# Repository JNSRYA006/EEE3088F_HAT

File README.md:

# Autonomous Plant Monitoring HAT for Discovery Board with STM32F051x8
This repository will be updated at each stage of the design process, and where necessary changes are made.

# Group Members:
* Ryan Jones (JNSRYA006)
* Alex Cargill (CRGALE002)
* Devlin Trafford (TRFDEV001)

# Project Details
### This project is part of a project for EEE3088F in 2022
This project will design a HAT *(Hardware Attached on Top)* for a STM Discovery Board which uses the STM32F051x8. The use case for this HAT is for semi-autonomous indoor plant growing. It will have a temperature sensor located as close to the plant as possible as well as a light sensor facing the main direction which the plant receives light from . These sensors will connect to a STM Discovery board, which will act as the brain of the system. This design was created for small scale agricultural setups. Appropriate user stories were applied to develop the Specifications. Given these use cases, the PCB is able to:

* Monitor the **temperature** around a plant
* Get precise readings of the **light level** a plant is receiving. 

See a 3D render of the PCB from KiCad below,

|  |
| :----------------------------------------------------------: |

## Repository Structure
### Each sub-folder contains different aspects relating to different parts of the project
* ***PCB:*** The KiCad Project, Schematics, PCB & Layout and Project Libraries
* ***Firmware:*** Any software developed for the hardware or instructions on where to find relevant sofware in cases where it makes more sense to have this in its own dedicated repo
* ***Docs:***  Project documentation, Draft documents, ERC & DRC reports, project handins, schematic screenshot & documents and component datasheets
* ***Production:*** The final gerber files, BOM, Budget, or anything required by the fabrication houses
* ***Simulation:*** Any simulation files (SPICE) or design stage generated results (matlab or excel) 
* ***CAD:*** Any 3D models or mechanical designs for enclosures or support
# Hardware Requirements
 * [ ] STMDiscovery Board with an STM32F051x8 μC
 * [ ] 1 x MicroUSB to USB-A Cable
 * [ ] 1x MiniUSB to USB-A Cable
 * [ ] 8x Male to Female Jumpers

# Software Requirements

 - [ ] Computer 
	 - *Windows, Linux or MACOS*
 - [ ] STM32Cube IDE
	 - [Download available online](https://www.st.com/en/development-tools/stm32cubeide.html#get-software)
 - [ ] PuTTY
	 - [Download available online](https://www.chiark.greenend.org.uk/~sgtatham/putty/latest.html)

# How to short the UVLO circuit

- On the LHS of the board, remove resistor **R12 & R10** using pliers and twisting and pulling the resistors

- Q1 & IC1 (Circled in **Orange**) are the MOSFET & Op-Amp in the UVLO circuit that needs to be removed by soldering one end of a wire to the top pad (Pad 2) of R12 to the top pad (Pad 2) of R10 (Circled in **Green**)

  |  |
  | :----------------------------------------------------------: |

# How to connect the power module to the rest of the board

- On the top, RHS of the board, solder a wire between **TP9** *OR* the **+3V** pin pad and the right hand pin of **J7**
  - This will connect the power from the power module to the rest of the circuit
- If connected correctly, when a battery is inserted or a USB is connected, a **Red** diode (**D9**) will turn on to indicate the sensing and microcontroller sub-circuits are receiving power.

# How to connect the PCB to the STMDiscovery Board

The following locations **on the PCB** need to be soldered to the male end of the jumper:

(*Refer to the KiCad PCB file [here](https://github.com/JNSRYA006/EEE3088F_HAT/blob/main/PCB/main/main.kicad_pcb) for the exact location of these*)

- PA1
- PA2
- PA9
- PA10
- PB6
- PB7

The female end of these jumpers are then connected to the corresponding pins on the STMDiscovery board.

# How to connect the PCB & STMDiscovery to your computer using UART

- Download and install CH340 drivers
  - [Download available online](https://learn.sparkfun.com/tutorials/how-to-install-ch340-drivers/all#drivers-if-you-need-them)
- Plug the device to your computer using a USB port. 
  - Check that the device is visible under ports in the Device Manager (for *Windows*), 
    - [Instructions on how to open Device Manager here](https://www.lifewire.com/how-to-open-device-manager-2626075)
- Create a serial connection with a baud rate of 18400bits/s in PuTTY

# How to send your first data to the board!

- After connecting the board using the above instructions,
- Type “Hello HAT” into the console and press ENTER.
- The device will dump all information collected since the last time the device was connected to a USB host device in the terminal window

# Contributing to this project

You're more than welcome to contribute to this project! Please take a look at our CONTRIBUTING.md file linked here

# License

[Creative Commons Attribution 4.0 International license](https://choosealicense.com/licenses/cc-by-4.0/)

[MIT License](https://choosealicense.com/licenses/mit/)

#

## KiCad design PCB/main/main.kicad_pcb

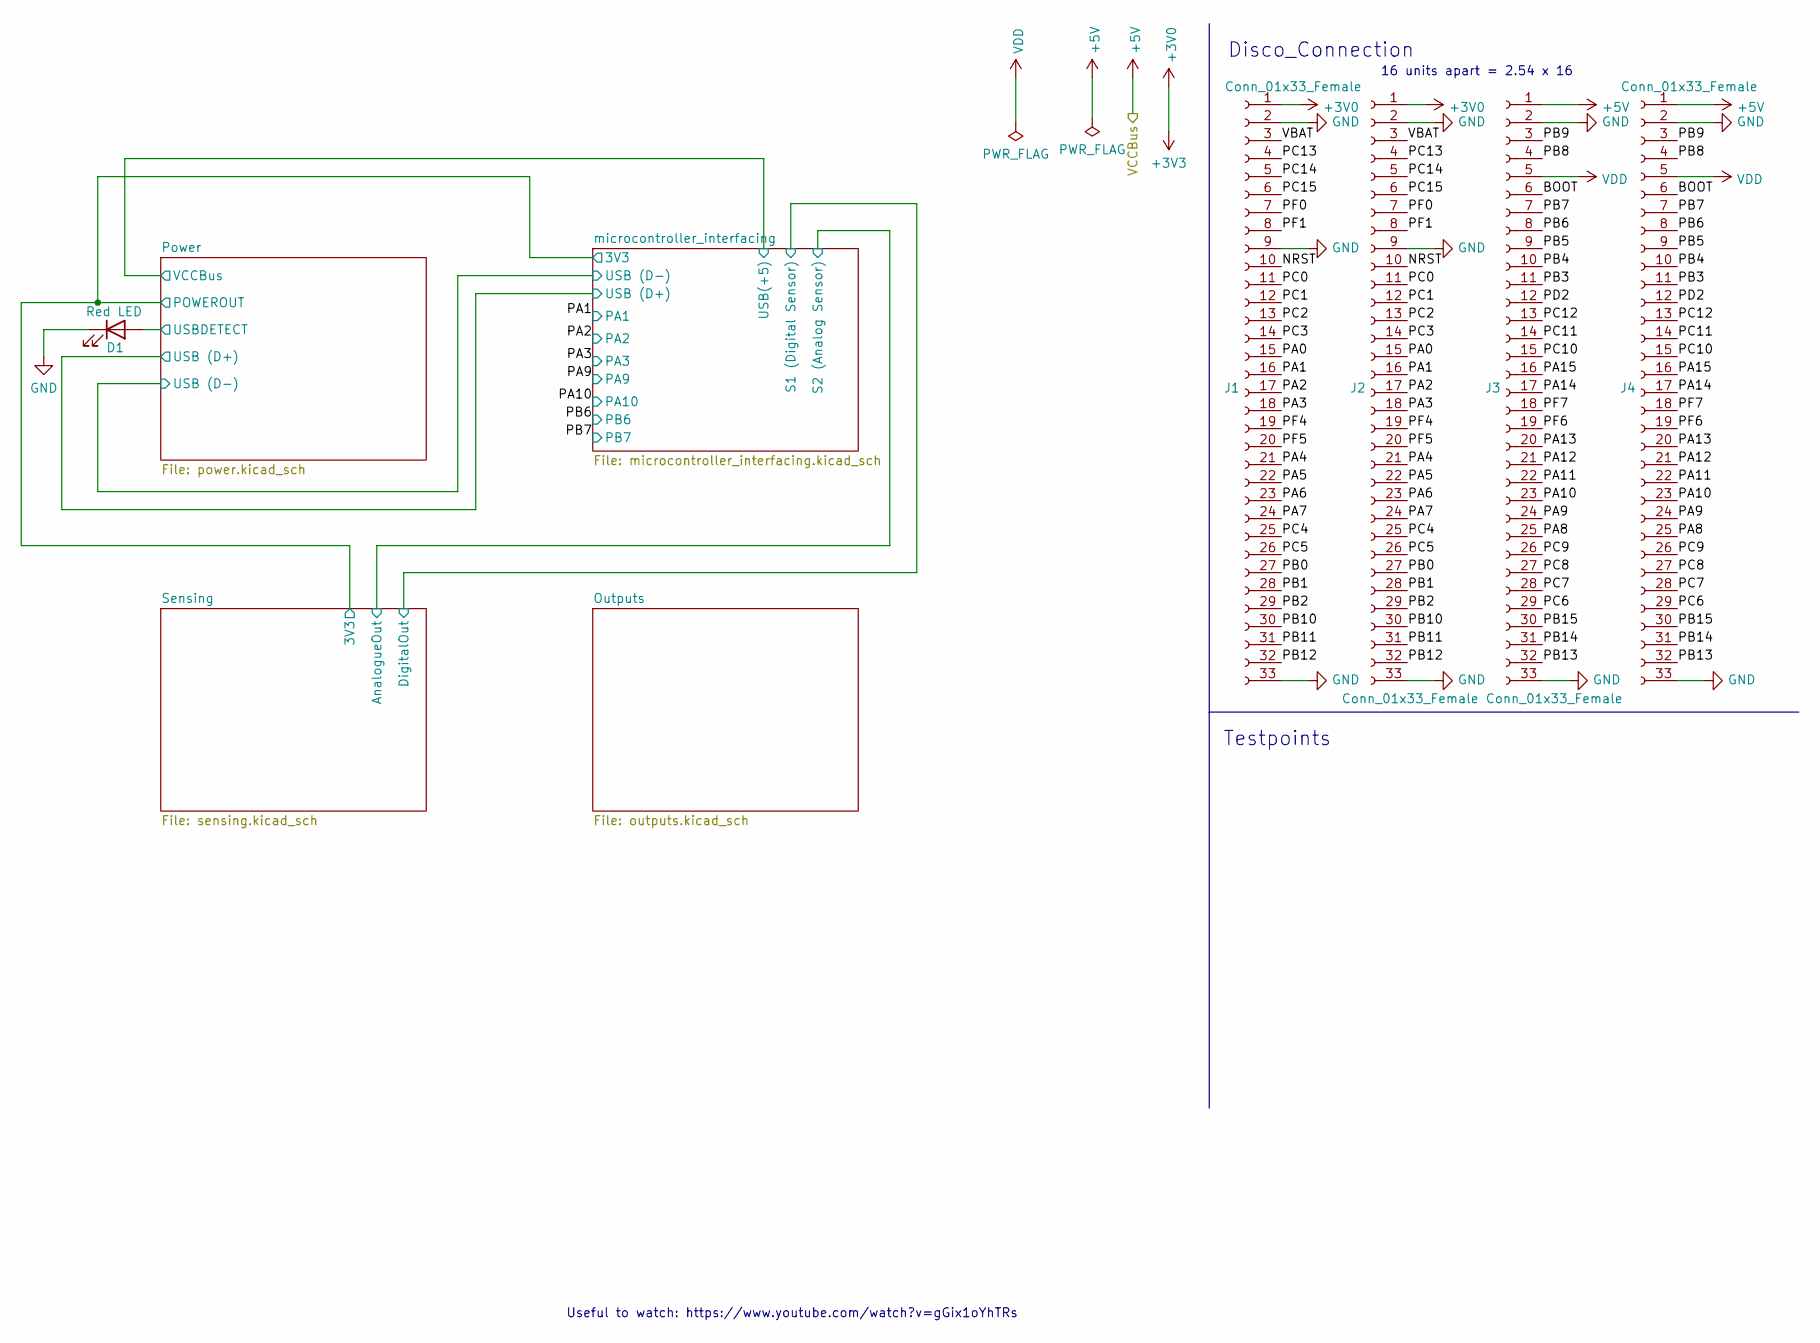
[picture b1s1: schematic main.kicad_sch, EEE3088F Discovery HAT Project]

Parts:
D1: Red LED; LEDC1608X70N; JLC Part Number C84256
J1, J4: Conn_01x33_Female; PinHeader_1x33_P2.54mm_Vertical
J2, J3: Conn_01x33_Female; PinSocket_1x33_P2.54mm_Vertical; LCSC C1234 (example)

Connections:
+3V0: J1.1, J2.1; also elsewhere on the board
+5V: J3.1, J4.1; also elsewhere on the board
/BOOT: J3.6, J4.6
/NRST: J1.10, J2.10
/PA0: J1.15, J2.15
/PA1: J1.16, J2.16; also elsewhere on the board
/PA2: J1.17, J2.17; also elsewhere on the board
/PA3: J1.18, J2.18; also elsewhere on the board
/PA4: J1.21, J2.21
/PA5: J1.22, J2.22
/PA6: J1.23, J2.23
/PA7: J1.24, J2.24
/PA8: J3.25, J4.25
/PA9: J3.24, J4.24; also elsewhere on the board
/PA10: J3.23, J4.23; also elsewhere on the board
/PA11: J3.22, J4.22
/PA12: J3.21, J4.21
/PA13: J3.20, J4.20
/PA14: J3.17, J4.17
/PA15: J3.16, J4.16
/PB0: J1.27, J2.27
/PB1: J1.28, J2.28
/PB2: J1.29, J2.29
/PB3: J3.11, J4.11
/PB4: J3.10, J4.10
/PB5: J3.9, J4.9
/PB6: J3.8, J4.8; also elsewhere on the board
/PB7: J3.7, J4.7; also elsewhere on the board
/PB8: J3.4, J4.4
/PB9: J3.3, J4.3
/PB10: J1.30, J2.30
/PB11: J1.31, J2.31
/PB12: J1.32, J2.32
/PB13: J3.32, J4.32
/PB14: J3.31, J4.31
/PB15: J3.30, J4.30
/PC0: J1.11, J2.11
/PC1: J1.12, J2.12
/PC2: J1.13, J2.13
/PC3: J1.14, J2.14
/PC4: J1.25, J2.25
/PC5: J1.26, J2.26
/PC6: J3.29, J4.29
/PC7: J3.28, J4.28
/PC8: J3.27, J4.27
/PC9: J3.26, J4.26
/PC10: J3.15, J4.15
/PC11: J3.14, J4.14
/PC12: J3.13, J4.13
/PC13: J1.4, J2.4
/PC14: J1.5, J2.5
/PC15: J1.6, J2.6
/PD2: J3.12, J4.12
/PF0: J1.7, J2.7
/PF1: J1.8, J2.8
/PF4: J1.19, J2.19
/PF5: J1.20, J2.20
/PF6: J3.19, J4.19
/PF7: J3.18, J4.18
/Power/USBDETECT: D1.2 (A); also elsewhere on the board
/VBAT: J1.3, J2.3
GND: D1.1 (K), J1.2, J1.9, J1.33, J2.2, J2.9, J2.33, J3.2, J3.33, J4.2, J4.33; also elsewhere on the board
VDD: J3.5, J4.5

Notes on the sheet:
Useful to watch: https://www.youtube.com/watch?v=gGix1oYhTRs
16 units apart = 2.54 x 16
Disco_Connection
Testpoints

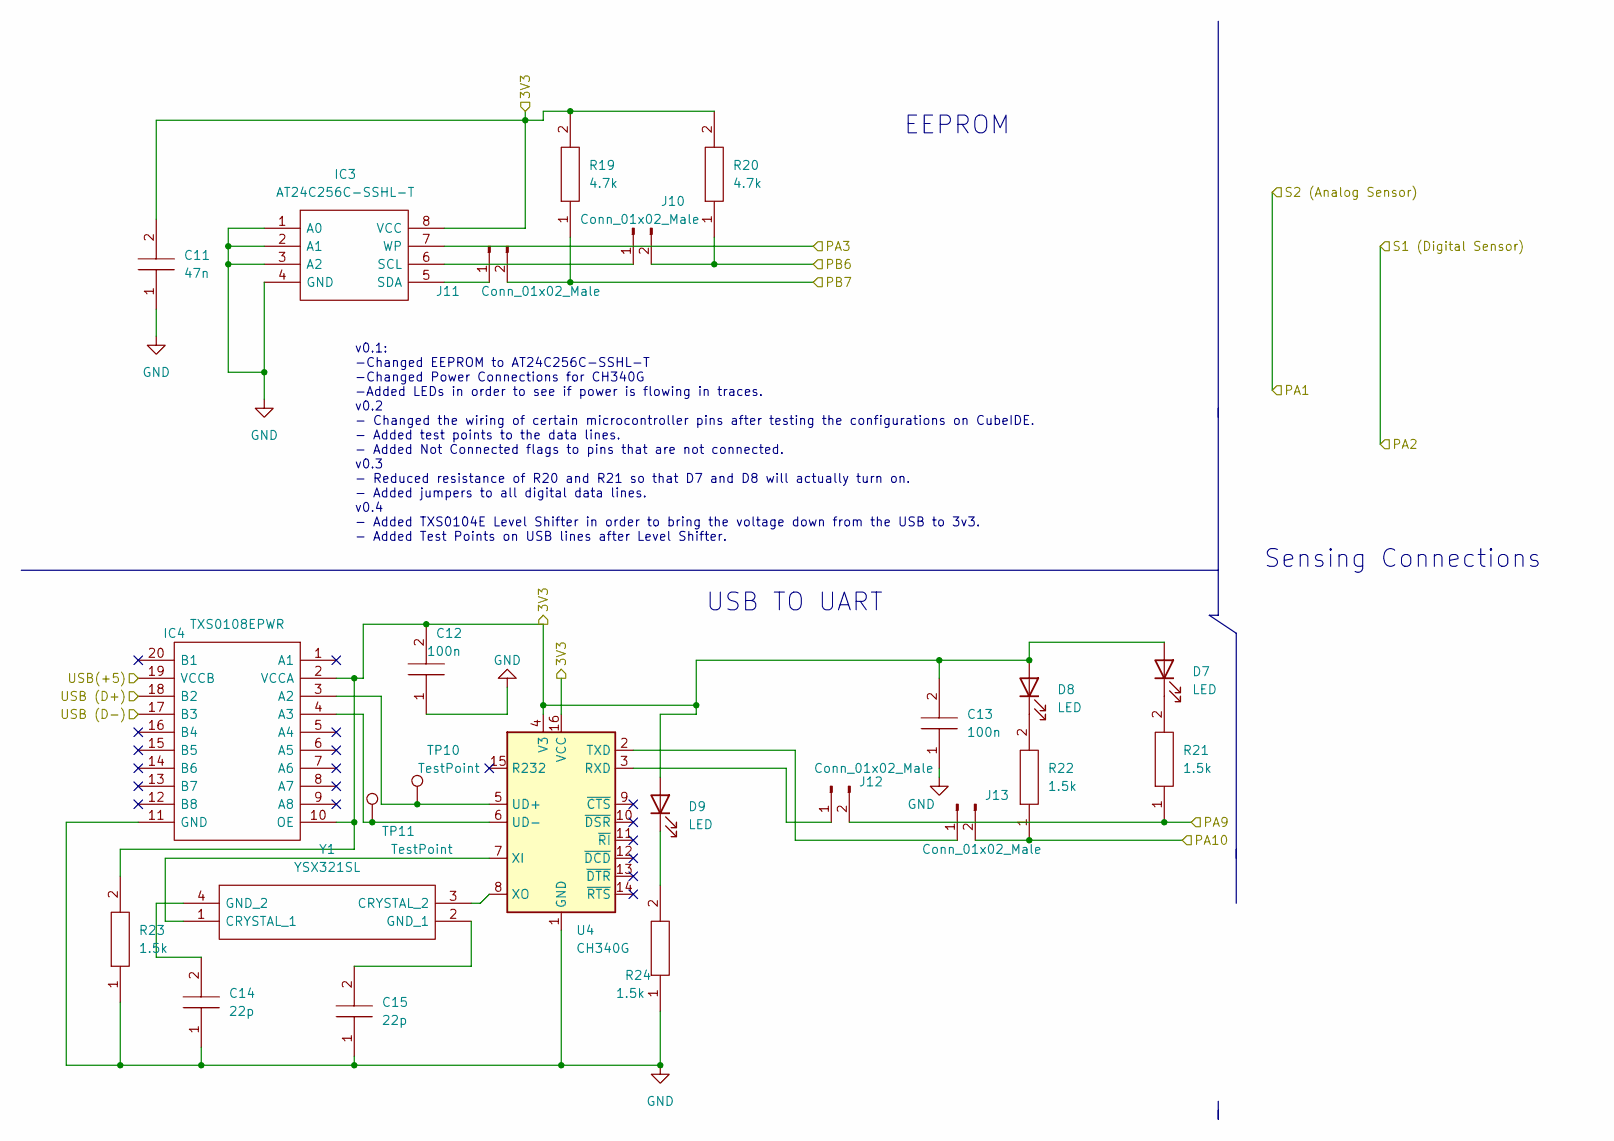
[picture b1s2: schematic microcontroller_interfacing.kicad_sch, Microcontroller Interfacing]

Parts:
C11: 47n; CAPC1608X90N; Manufacturer_Part_Number CL05B104KO5NNNC; Mouser Part Number 187-CL05B104KO5NNNC
C12, C13: 100n; C_0402_1005Metric; Manufacturer_Part_Number CL05B104KO5NNNC; Mouser Part Number 187-CL05B104KO5NNNC
C14, C15: 22p; CAPC1608X90N; Manufacturer_Part_Number CL05B104KO5NNNC; Mouser Part Number 187-CL05B104KO5NNNC
D7, D8, D9: LED; LED_0805_2012Metric; JLC Part Number C2286
IC3: AT24C256C-SSHL-T; SOIC127P600X175-8N; JLC Part Number C6482
IC4: TXS0108EPWR; SOP65P640X120-20N; Manufacturer_Part_Number TXS0108EPWR; Mouser Part Number 595-TXS0108EPWR
J10, J11, J12, J13: Conn_01x02_Male; 53398-0271; JLC Part Number C122410
R19, R20: 4.7k; RESC2013X65N; Manufacturer_Part_Number 0402WGF4701TCE
R21, R22, R23, R24: 1.5k; RESC2013X65N; Manufacturer_Part_Number 0402WGF4701TCE; JLC Part Number C25867
TP10, TP11: TestPoint; TestPoint_Pad_D2.0mm
U4: CH340G; SOIC127P600X180-16N; JLC Part Number C14267
Y1: YSX321SL; Manufacturer_Part_Number YSX321SL; JLC Part Number C9002

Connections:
+3V3: C11.2, C12.2, C13.2, D7.2 (A), D8.2 (A), D9.2 (A), IC3.8 (VCC), IC4.2 (VCCA), IC4.10 (OE), R19.2, R20.2, R23.2, U4.4 (V3), U4.16 (VCC); also elsewhere on the board
+5V: IC4.19 (VCCB); also elsewhere on the board
/PA3: IC3.7 (WP); also elsewhere on the board
/PA9: J12.2, R21.1; also elsewhere on the board
/PA10: J13.2, R22.1; also elsewhere on the board
/PB6: J10.2, R20.1; also elsewhere on the board
/PB7: J11.2, R19.1; also elsewhere on the board
/Power/USB (D+): IC4.18 (B2); also elsewhere on the board
/Power/USB (D-): IC4.17 (B3); also elsewhere on the board
GND: C11.1, C12.1, C13.1, C14.1, C15.1, IC3.1 (A0), IC3.2 (A1), IC3.3 (A2), IC3.4 (GND), IC4.11 (GND), R23.1, R24.1, U4.1 (GND); also elsewhere on the board
unnamed: C14.2, Y1.4 (GND_2)
unnamed: C15.2, Y1.2 (GND_1)
unnamed: D7.1 (K), R21.2
unnamed: D8.1 (K), R22.2
unnamed: D9.1 (K), R24.2
unnamed: IC3.5 (SDA), J11.1
unnamed: IC3.6 (SCL), J10.1
unnamed: IC4.3 (A2), TP10.1, U4.5 (UD+)
unnamed: IC4.4 (A3), TP11.1, U4.6 (UD-)
unnamed: J12.1, U4.3 (RXD)
unnamed: J13.1, U4.2 (TXD)
unnamed: U4.7 (XI), Y1.1 (CRYSTAL_1)
unnamed: U4.8 (XO), Y1.3 (CRYSTAL_2)

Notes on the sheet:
v0.1: -Changed EEPROM to AT24C256C-SSHL-T -Changed Power Connections for CH340G -Added LEDs in order to see if power is flowing in traces. v0.2 - Changed the wiring of certain microcontroller pins after testing the configurations on CubeIDE. - Added test points to the data lines. - Added Not Connec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
EEPROM
USB TO UART
Sensing Connections

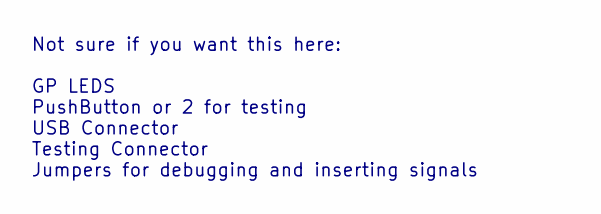
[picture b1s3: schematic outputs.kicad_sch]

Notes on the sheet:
Not sure if you want this here: GP LEDS PushButton or 2 for testing USB Connector Testing Connector Jumpers for debugging and inserting signals

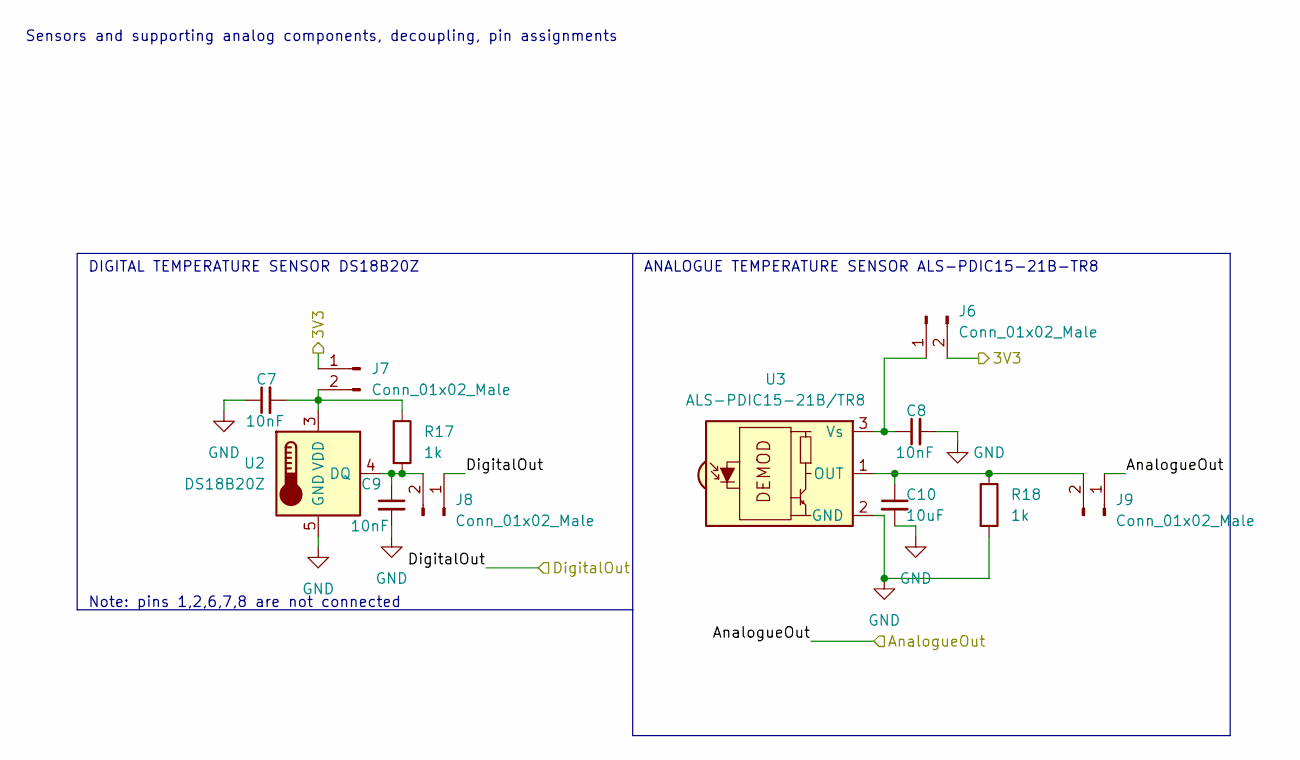
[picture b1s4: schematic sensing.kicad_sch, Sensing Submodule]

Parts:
C7, C8, C9: 10nF; C_0402_1005Metric; JLC Part Number C15195
C10: 10uF; CAPC2012X145N; JLC Part Number C19702
J6, J7, J8, J9: Conn_01x02_Male; 53398-0271; JLC Part Number C122410
R17, R18: 1k; RESC1608X55N; JLC Part Number C21190
U2: DS18B20Z; SOIC-8_3.9x4.9mm_P1.27mm; JLC Part Number C695837
U3: ALS-PDIC15-21B/TR8; LED-SMD_1206-4P-L3.2-W1.5-TR; JLC Part Number C131243

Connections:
+3V3: J6.2, J7.1; also elsewhere on the board
/PA1: J9.1; also elsewhere on the board
/PA2: J8.1; also elsewhere on the board
GND: C7.1, C8.2, C9.2, C10.2, R18.2, U2.5 (GND), U3.2 (GND); also elsewhere on the board
unnamed: C7.2, J7.2, R17.1, U2.3 (VDD)
unnamed: C8.1, J6.1, U3.3 (Vs)
unnamed: C9.1, J8.2, R17.2, U2.4 (DQ)
unnamed: C10.1, J9.2, R18.1, U3.1 (OUT)

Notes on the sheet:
ANALOGUE TEMPERATURE SENSOR ALS-PDIC15-21B-TR8
DIGITAL TEMPERATURE SENSOR DS18B20Z
Note: pins 1,2,6,7,8 are not connected
Sensors and supporting analog components, decoupling, pin assignments

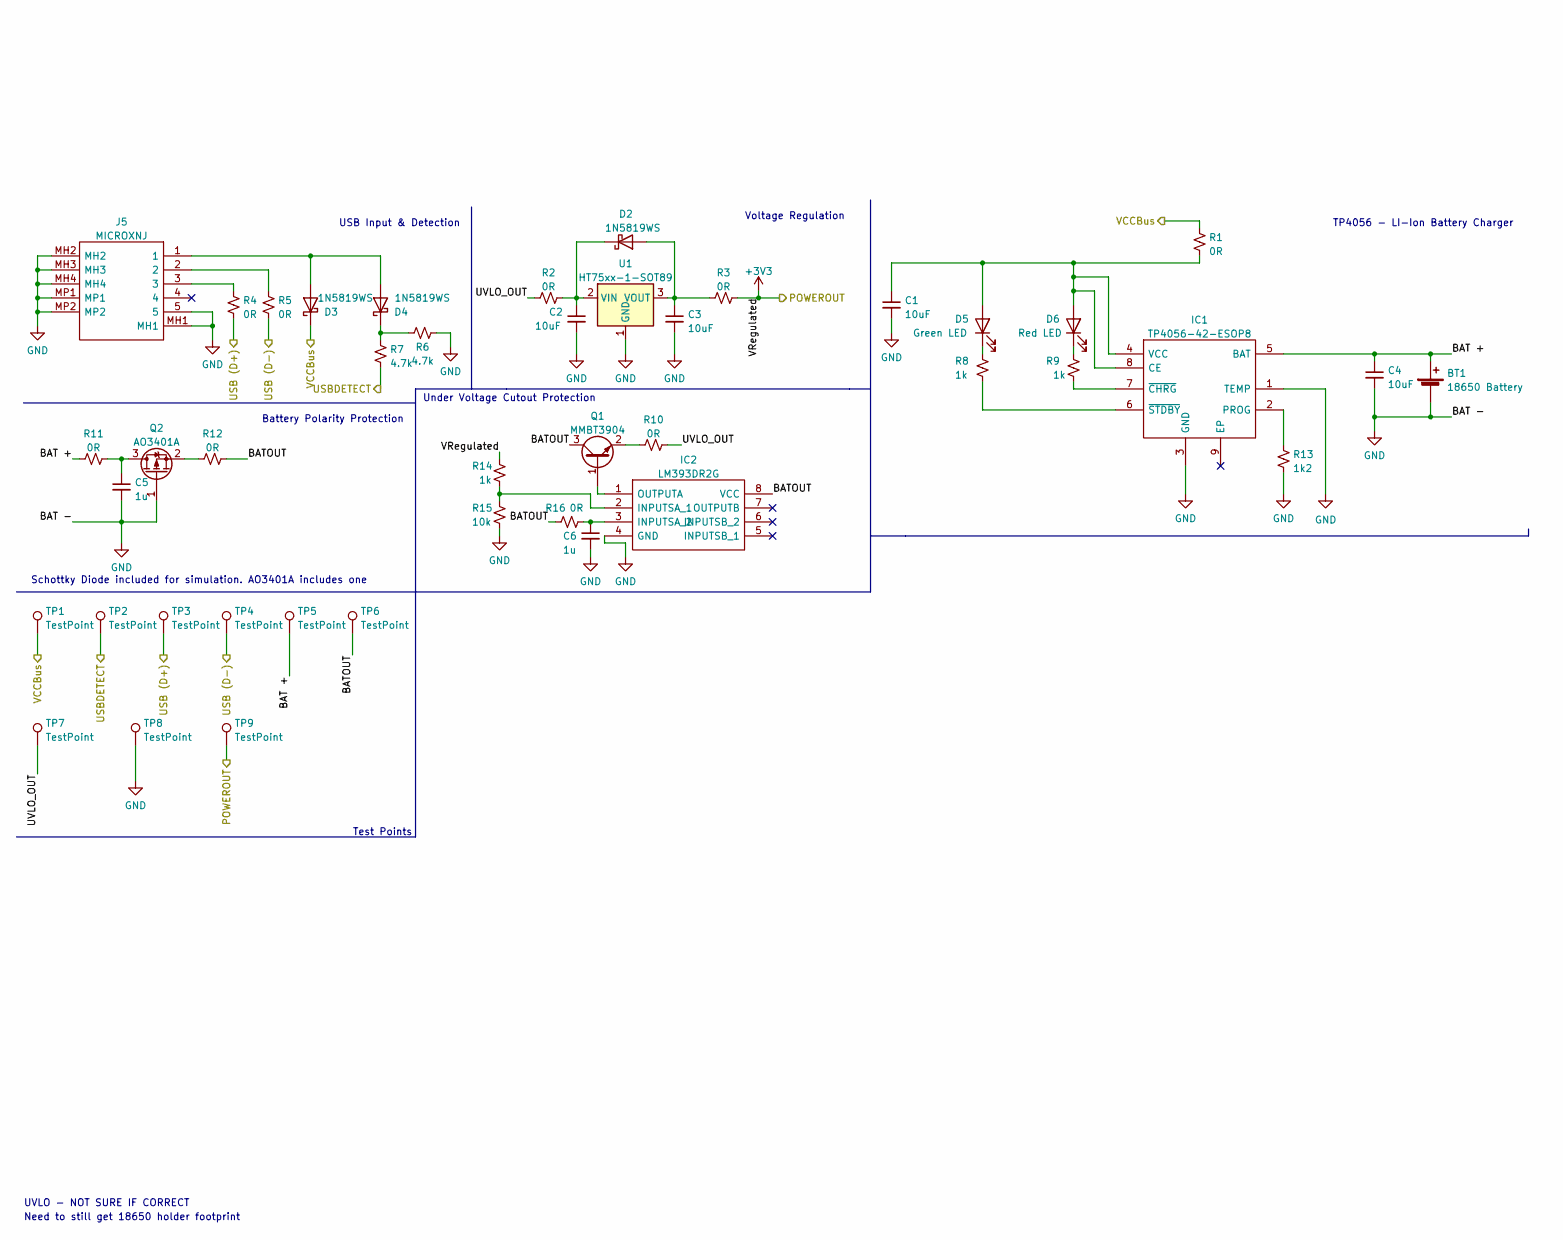
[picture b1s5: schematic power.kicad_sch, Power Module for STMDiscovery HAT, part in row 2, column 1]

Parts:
BT1: 18650 Battery; KEYSTONE-1042
C1, C2, C3, C4: 10uF; CAPC2012X145N; JLC Part Number C19702
C5, C6: 1u; CAPC1608X90N; JLC Part Number C52923
D2, D3, D4: 1N5819WS; D_SOD-323; JLC Part Number C191023
D5: Green LED; LEDC1608X50N; JLC Part Number C72043
D6: Red LED; LEDC1608X70N; JLC Part Number C84256
IC1: TP4056-42-ESOP8; SOIC127P600X175-9N; Manufacturer_Part_Number TP4056-42-ESOP8; JLC Part Number C16581
IC2: LM393DR2G; SOIC127P600X175-8N; Manufacturer_Part_Number LM393DR2G; Mouser Part Number 863-LM393DR2G
J5: MICROXNJ; SHOUHAN_MICROXNJ; Manufacturer_Part_Number MICROXNJ; JLC Part Number C404969
Q1: MMBT3904; SOT-23; JLC Part Number C20526
Q2: AO3401A; SOT95P280X125-3N; JLC Part Number C15127
R1, R2, R3, R4, R5, R10, R11, R12, R16: 0R; RESC2013X65N; JLC Part Number C17477
R6, R7: 4.7k; RESC2013X65N; JLC Part Number C17673
R8, R9, R14: 1k; RESC1608X55N; JLC Part Number C21190
R13: 1k2; RESC1608X55N; JLC Part Number C22765
R15: 10k; RESC1005X40N; JLC Part Number C25905
TP1, TP2, TP3, TP4, TP5, TP6, TP7, TP8, TP9: TestPoint; TestPoint_Pad_D2.0mm
U1: HT75xx-1-SOT89; SOT-89-3; JLC Part Number C14289

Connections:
+3V0: R3.1, R14.1, TP9.1; also elsewhere on the board
+5V: D3.1 (K), R1.2, TP1.1; also elsewhere on the board
/Power/BAT +: BT1.1 (+), C4.1, IC1.5 (BAT), R11.2, TP5.1
/Power/BATOUT: IC2.8 (VCC), Q1.3 (C), R12.1, R16.2, TP6.1
/Power/USB (D+): R4.1, TP3.1; also elsewhere on the board
/Power/USB (D-): R5.1, TP4.1; also elsewhere on the board
/Power/USBDETECT: R7.1, TP2.1; also elsewhere on the board
/Power/UVLO_OUT: R2.2, R10.1, TP7.1
GND: BT1.2 (-), C1.2, C2.2, C3.2, C4.2, C5.2, C6.2, IC1.1 (TEMP), IC1.3 (GND), IC2.4 (GND), J5.5, J5.MH1, J5.MH2, J5.MH3, J5.MH4, J5.MP1, J5.MP2, Q2.1 (G), R6.2, R13.2, R15.2, TP8.1, U1.1 (GND); also elsewhere on the board
unnamed: C1.1, D5.2 (A), D6.2 (A), IC1.4 (VCC), IC1.8 (CE), R1.1
unnamed: C2.1, D2.1 (K), R2.1, U1.2 (VIN)
unnamed: C3.1, D2.2 (A), R3.2, U1.3 (VOUT)
unnamed: C5.1, Q2.3 (D), R11.1
unnamed: C6.1, IC2.3 (INPUTSA_2), R16.1
unnamed: D3.2 (A), D4.2 (A), J5.1
unnamed: D4.1 (K), R6.1, R7.2
unnamed: D5.1 (K), R8.1
unnamed: D6.1 (K), R9.1
unnamed: IC1.2 (PROG), R13.1
unnamed: IC1.6 (~STDBY), R8.2
unnamed: IC1.7 (~CHRG), R9.2
unnamed: IC2.1 (OUTPUTA), Q1.1 (B)
unnamed: IC2.2 (INPUTSA_1), R14.2, R15.1
unnamed: J5.2, R5.2
unnamed: J5.3, R4.2
unnamed: Q1.2 (E), R10.2
unnamed: Q2.2 (S), R12.2

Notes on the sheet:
Battery Polarity Protection
USB Input & Detection
Voltage Regulation
TP4056 - LI-Ion Battery Charger
Under Voltage Cutout Protection
UVLO - NOT SURE IF CORRECT
Test Points
Check IC can take in ~4V
Schottky Diode included for simulation. AO3401A includes one
Need to still get 18650 holder footprint

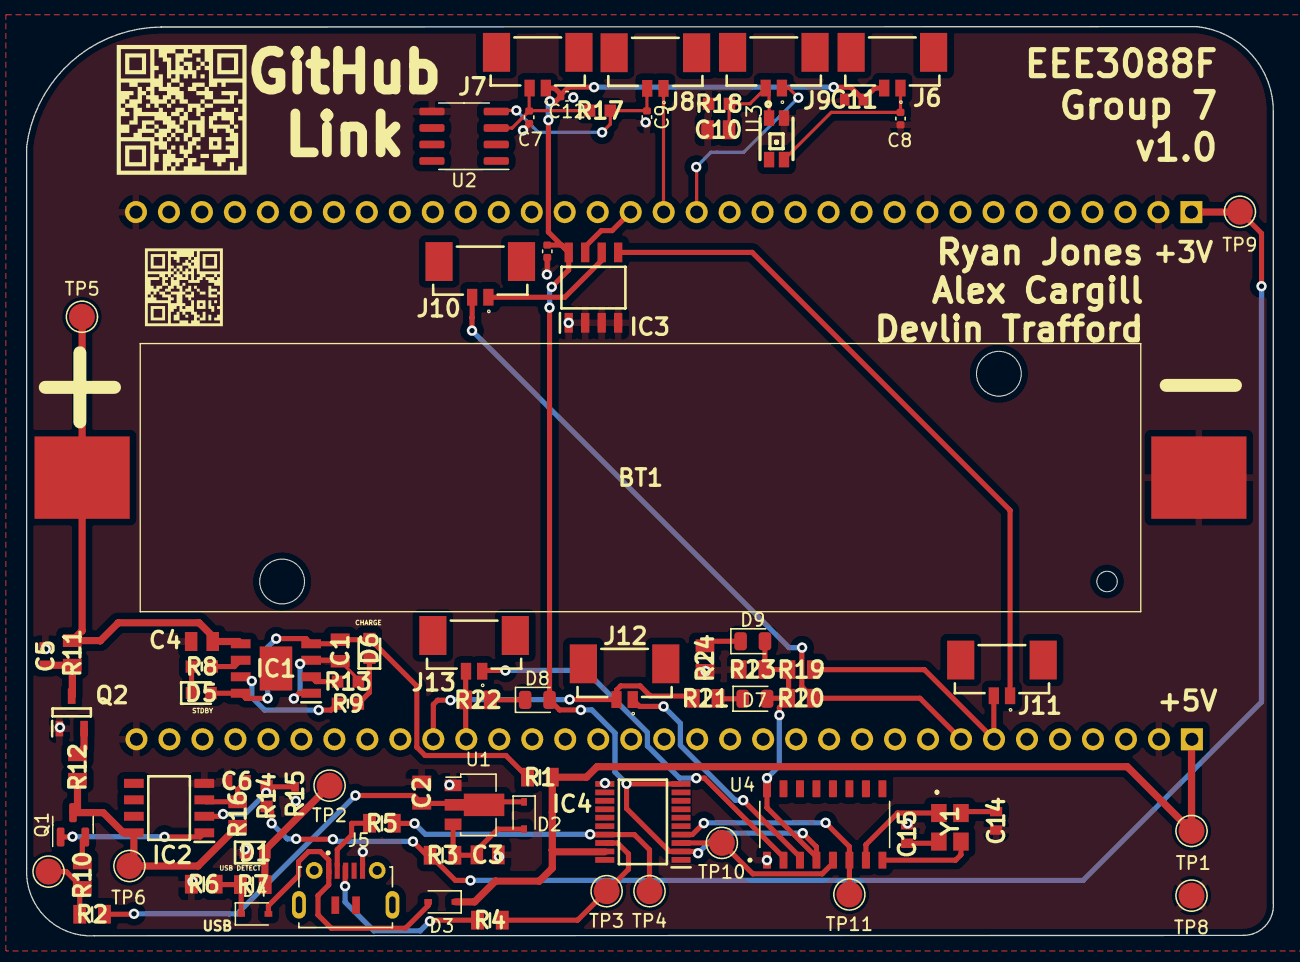
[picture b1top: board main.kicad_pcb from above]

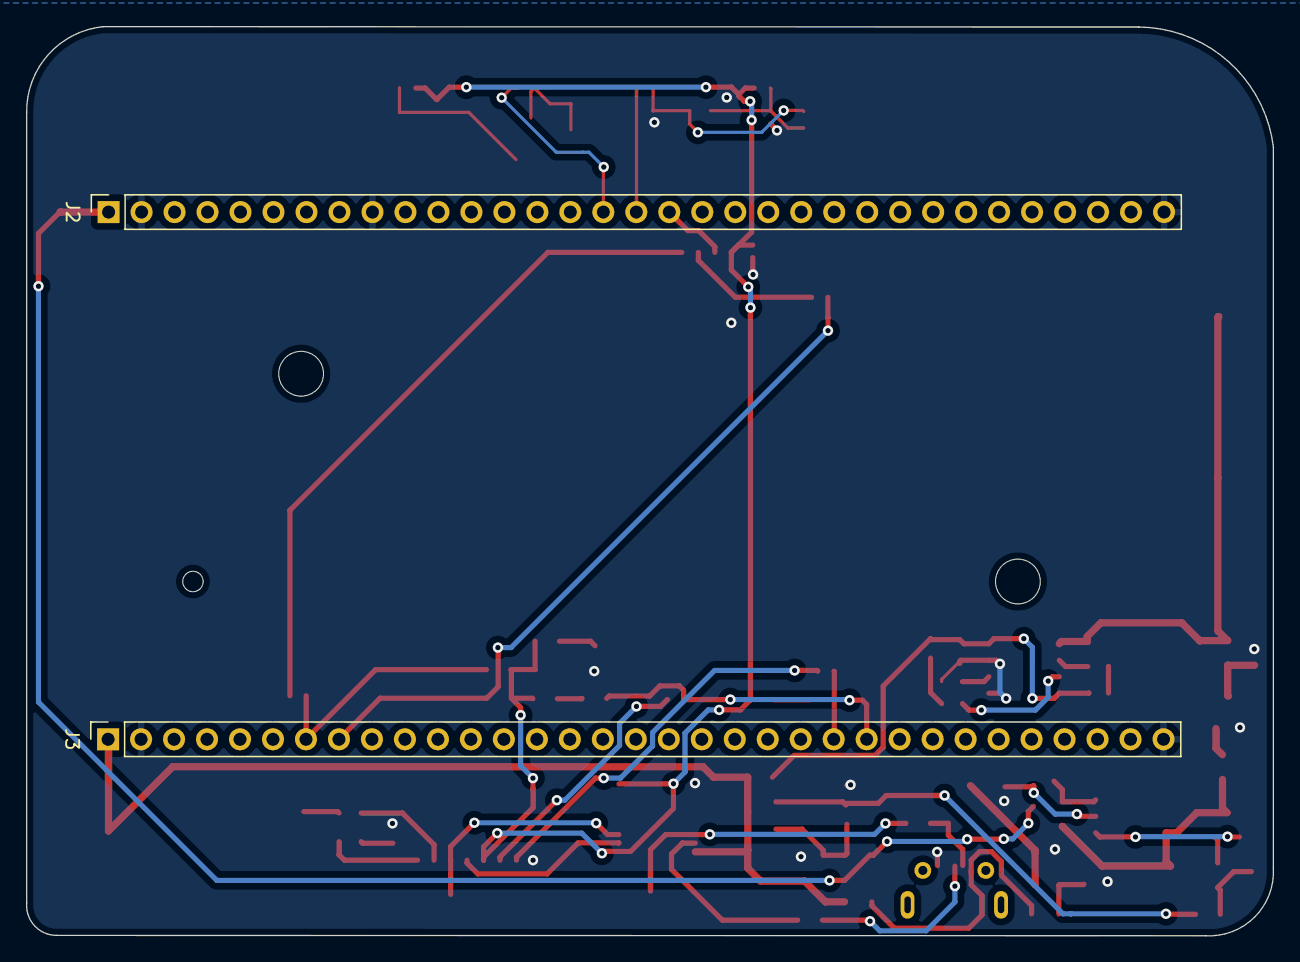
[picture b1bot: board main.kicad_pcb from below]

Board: 2 copper layers, 96.0 x 70.0 mm, 82 parts (2 on the bottom side), 52 nets.

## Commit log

2022-02-25 Create PCB_readme.md
    Still includes copied notes on options for KiCad Library setup
2022-02-25 Update README.md
    Still a draft version - need to beef out with more details
2022-02-25 Update README.md
    fix formatting of bullet points for Repo structure section
2022-02-25 Update README.md
    added group member names
2022-02-25 Add Discovery files from Template Repo
2022-02-25 Add Week 2 Assignment - Project Concept
2022-02-25 Add License, gitignore, gitmodules from template
2022-02-25 Delete .gitmodules
    need to update to suit project needs. Look at template
2022-02-25 Added power block to block diagram
2022-02-28 Upload KiCad Templates
2022-02-28 Add Library Submodule Repo
2022-03-02 Added sheet details to schematic
2022-03-02 Add Power Module Datasheets
2022-03-03 Add battery datasheet
2022-03-03 Power Module v0.01
2022-03-04 Power Module v0.02
2022-03-04 Power module v0.02 update
2022-03-04 Power Module v0.03
2022-03-04 Power Module v0.04 Update
2022-03-04 Add Power Module v0.04 Draft BOM
2022-03-04 Add Power Module v0.04 Draft BOM - Update Header
2022-03-04 Add Power Module v0.04 Draft BOM - Update Header & Columns
2022-03-04 uC SubModule v0.01
2022-03-04 Add Microcontroller Interface v0.01 Draft BOM
2022-03-04 Add Mictrocontroller Interface v0.01 Draft BOM
2022-03-04 Create BOMs_Readme
2022-03-04 Rename BOMs_Readme to BOMs_Readme.md
2022-03-04 Sensing SubModule v0.01
2022-03-04 Add Sensing v0.01 Draft BOM
2022-03-11 Power v0.1, Sensing v0.1, uC Control v0.1, Simulations
2022-03-11 Simulations JPGs
2022-03-11 ERC report v0.01
2022-03-11 Power v0.1, Sensing v0.1, uC Control v0.1, ERC
2022-03-11 Add BOM v0.10
2022-03-11 Add Intial Design Submission
2022-03-17 Schematic updates
2022-03-17 Power, uC, Sensing v0.1.1
2022-03-19 Schematics v0.1.1 & PCB v0.01
2022-03-19 Upload Interactive BOM
2022-03-20 Add Power Module Schematic v0.1.1 Screenshot
2022-03-20 Add v0.1.1 BOM
2022-03-20 Add BOM v0.1.1
2022-03-20 Gerber, DRC text report, PCB v0.02
2022-03-20 Week 5 handin Doc upload
2022-03-21 Update Week 5 handin document title
2022-03-25 Upload Week 6 Handin
2022-04-11 v1.0 BOM, Gerbers & Final Designs
2022-04-11 v1.0 BOMs
2022-04-11 Interactive BOM v1.0
2022-04-11 Updated v1.0 - moved a decouplicng capacitor closer to pin
2022-04-11 Updates to Microcontroller Circuit
2022-04-18 Upload Power Schematic Screenshot v1.0
2022-04-21 Add Screenshots of uC & Sensing v1.0 submodules
2022-05-18 Added Schematic PDF & Draft Report
2022-05-21 Update README.md
    Added new headings for setting up code & board
2022-05-21 Upload 3D Render of PCB image
2022-05-22 Add HTML for Git Pages
2022-05-23 Added code reference document
2022-05-23 Added README.png
2022-05-23 Added CONTRIBUTING.md
2022-05-23 Upload Documentation Submission
